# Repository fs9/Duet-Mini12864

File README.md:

# Duet-Mini12864
A simple adapter board for using Fysetc's Mini 12864 LCD with Duet 2 boards

RepRapFirmware 3.2 included support for ST7567-based displays, but there are wiring differences between the Duet 2 and Fysetc's Mini 12864 displays. To keep wiring straightforward, I designed this simple board that handles the redirections, which, I hope, will translate into a tidier electronics bay and make it easier to add a 12864 LCD for those who have a hard time wiring cables by hand.

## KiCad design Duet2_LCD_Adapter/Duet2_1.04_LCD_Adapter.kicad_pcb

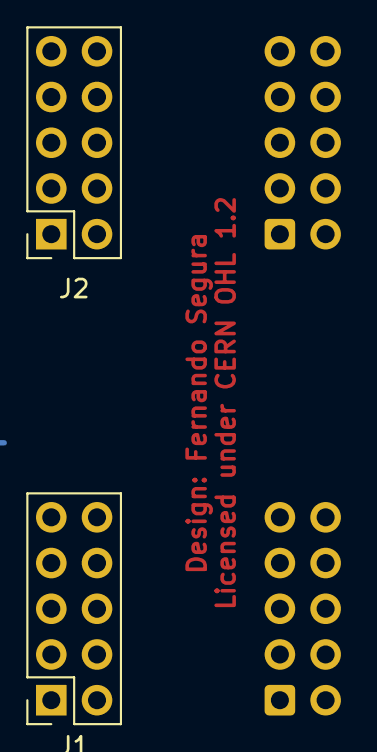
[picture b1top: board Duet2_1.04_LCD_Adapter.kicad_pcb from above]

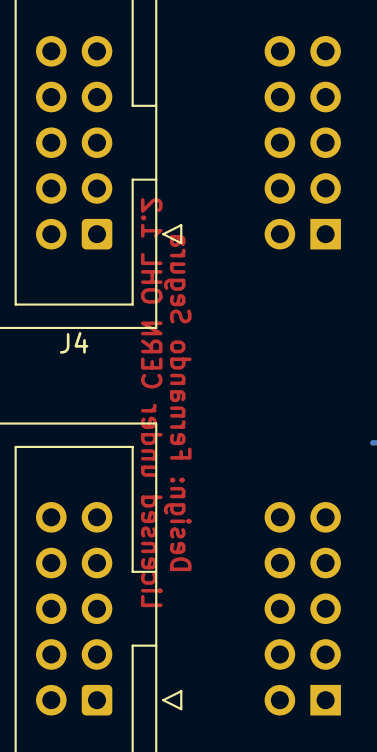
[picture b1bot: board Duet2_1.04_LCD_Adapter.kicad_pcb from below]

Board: 2 copper layers, 4 parts (2 on the bottom side), 15 nets, no tracks yet.

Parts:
J1: CONN_LCD; PinSocket_2x05_P2.54mm_Vertical
J2: CONN_SD; PinSocket_2x05_P2.54mm_Vertical
J3: EXP_1; IDC-Header_2x05_P2.54mm_Vertical
J4: EXP_2; IDC-Header_2x05_P2.54mm_Vertical

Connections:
unnamed: J1.1, J4.6
unnamed: J1.2, J3.2
unnamed: J1.4, J4.8
unnamed: J1.5, J3.5
unnamed: J1.6, J3.6
unnamed: J1.7, J3.7
unnamed: J1.8, J3.8
unnamed: J1.9, J3.9
unnamed: J1.10, J3.10
unnamed: J2.1, J3.1
unnamed: J2.2, J4.2
unnamed: J2.3, J4.7
unnamed: J2.4, J4.9
unnamed: J2.5, J4.5
unnamed: J2.6, J4.10

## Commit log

2021-07-01 2021-07-01: Added KiCad project files.
2021-07-01 2021-07-01: Added License information.
2021-07-01 2021-07-01: Added Images directory with renders of both sides of the board.
2021-07-01 2021-07-01: Added images to Readme.

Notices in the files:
Duet2_LCD_Adapter/Duet2_1.04_LCD_Adapter.kicad_pcb:
Licensed under CERN OHL 1.2
